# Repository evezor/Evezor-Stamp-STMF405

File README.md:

# Evezor-Stamp-STMF405
*please note this board is has been deprecated. 

The Evezor Stamp is a castellated carrier for the stmf405 chip with CAN networking and memory for Evezor's Edge network

The intent was that I could have this made by a higher quality shop with better pick and place machines than I had at the time. 
This was originally designed early in the pandemic and then the STM chips became completely unavailable. 
It worked pretty good, but in the end I'm glad I changed chipsets for a number of reasons. 
For one, I think I would have not liked using these so much. The boards I designed for this had this module on the back. Don't do double sided stuff unless absolutely necessary. Additionally, changing chips right in the early stages provided me with the knowledge of the location of the boundaries between chips. This was and is good knowledge. 

I also developed a test and programming jig. It worked ok as well.

Evezor® and all associated marks, logos, and designs are registered trademarks and protected by copyright. Unauthorized use or reproduction of these trademarks and copyrighted materials is strictly prohibited

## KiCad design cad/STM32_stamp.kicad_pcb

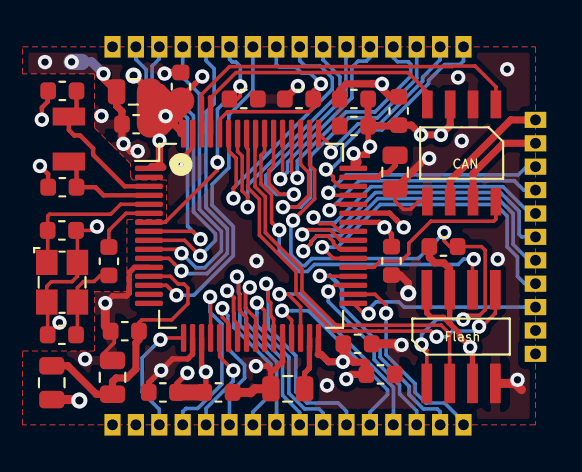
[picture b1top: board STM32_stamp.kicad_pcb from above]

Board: 4 copper layers, 32 parts (0 on the bottom side), 55 nets.

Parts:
C1, C3: 20pF; C_0603_1608Metric
C2, C4: 12pF; C_0603_1608Metric
C5, C7, C10, C16: 10uF; C_0805_2012Metric
C6, C8, C9, C11, C12, C13, C14, C15, C17, C18, C19, C20: 100nF; C_0603_1608Metric
FB1: Ferrite; L_0805_2012Metric
J1, J3: Conn_01x16; CASTELLATED_16
J2: Conn_01x11; CASTELLATED_11
R1: 220; R_0603_1608Metric
R3, R4: 100K; R_0603_1608Metric
U1: STM32F405RGTx; LQFP-64_10x10mm_P0.5mm
U2: Trans_CAN_SN65HVD230DR; CAN-TRANS-SN65HVD230DR
U3: Edge_V1_Mem; STM32_SOIC8_MEM
Y1: 32.768; CRYSTAL_SEIKO_32.768_SC-32S32.768kHz20PPM12.5pF
Y2: 12MHz; Crystal_3.2X2.5X0.8_C9002

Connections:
+3.3VA: C14.1, C16.1, FB1.2, U1.13
+3V3: C5.1, C6.1, C9.1, C11.1, C12.1, C13.1, C15.1, C17.1, C18.1, C19.2, C20.1, FB1.1, J1.1, J2.2, R4.1, U1.1, U1.19, U1.32, U1.42, U1.43, U1.48, U1.64, U2.3, U3.3, U3.7, U3.8
BOOT0: J3.8, R3.1, U1.60
CAN_H: J2.10, U2.7
CAN_L: J2.11, U2.6
CAN_RX: U1.61, U2.4
CAN_SLP: U1.37, U2.8
CAN_TX: U1.62, U2.1
D+: J2.9, U1.45
D-: J2.8, U1.44
FLASH_CS: R4.2, U1.50, U3.1
FLASH_MISO: U1.56, U3.2
FLASH_MOSI: U1.57, U3.5
FLASH_SCK: U1.55, U3.6
GND: C1.2, C2.2, C3.2, C4.2, C5.2, C6.2, C7.2, C8.2, C9.2, C10.2, C11.2, C12.2, C13.2, C14.2, C15.2, C16.2, C17.2, C18.2, C19.1, C20.2, J1.2, J2.1, J3.1, R3.2, U1.12, U1.18, U1.28, U1.63, U2.2, U2.5, U3.4, Y2.2, Y2.4
HSE_IN: C1.1, U1.5, Y2.1
HSE_OUT: R1.1, U1.6
LSE_IN: C2.1, U1.3, Y1.1
LSE_OUT: C4.1, U1.4, Y1.2
NRST: C8.1, J3.6, U1.7
unnamed: C3.1, R1.2, Y2.3
unnamed: C7.1, U1.31
unnamed: C10.1, U1.47
PA0: J3.7, U1.14
PA3: J1.3, U1.17
PA4: J1.4, U1.20
PA5: J1.5, U1.21
PA6: J1.6, U1.22
PA7: J1.7, U1.23
PA8: J2.7, U1.41
PB0: J1.10, U1.26
PB1: J1.11, U1.27
PB6: J3.10, U1.58
PB7: J3.9, U1.59
PB10: J1.12, U1.29
PB11: J1.13, U1.30
PB12: J2.3, U1.33
PB13: J1.16, U1.34
PB14: J1.14, U1.35
PB15: J1.15, U1.36
PC0: J3.2, U1.8
PC1: J3.3, U1.9
PC2: J3.4, U1.10
PC3: J3.5, U1.11
PC4: J1.8, U1.24
PC5: J1.9, U1.25
PC7: J2.4, U1.38
PC8: J2.5, U1.39
PC9: J2.6, U1.40
PC10: J3.14, U1.51
PC11: J3.13, U1.52
PC12: J3.12, U1.53
PD2: J3.11, U1.54
SWDIO: J3.16, U1.46
SW_CLK: J3.15, U1.49

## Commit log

2023-09-10 init
2023-09-10 add pics
2023-09-10 add pic
2023-09-10 Create LICENCE
